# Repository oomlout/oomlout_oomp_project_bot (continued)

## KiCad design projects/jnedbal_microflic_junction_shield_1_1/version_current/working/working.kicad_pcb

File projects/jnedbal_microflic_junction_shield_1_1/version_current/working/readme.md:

# MicroFLiC_junction_shield_1_1 by jnedbal  
This is a harvested standardized copy of a project from github.  
The original project can be found at:  
https://github.com/jnedbal/MicroFLiC_junction_shield_1_1  
Please consult that link for additional, details, files, and license information.  
Note: It was auto harvested and if the original repo had more than one board file or anything out of the ordinary the files here are likely not representative.

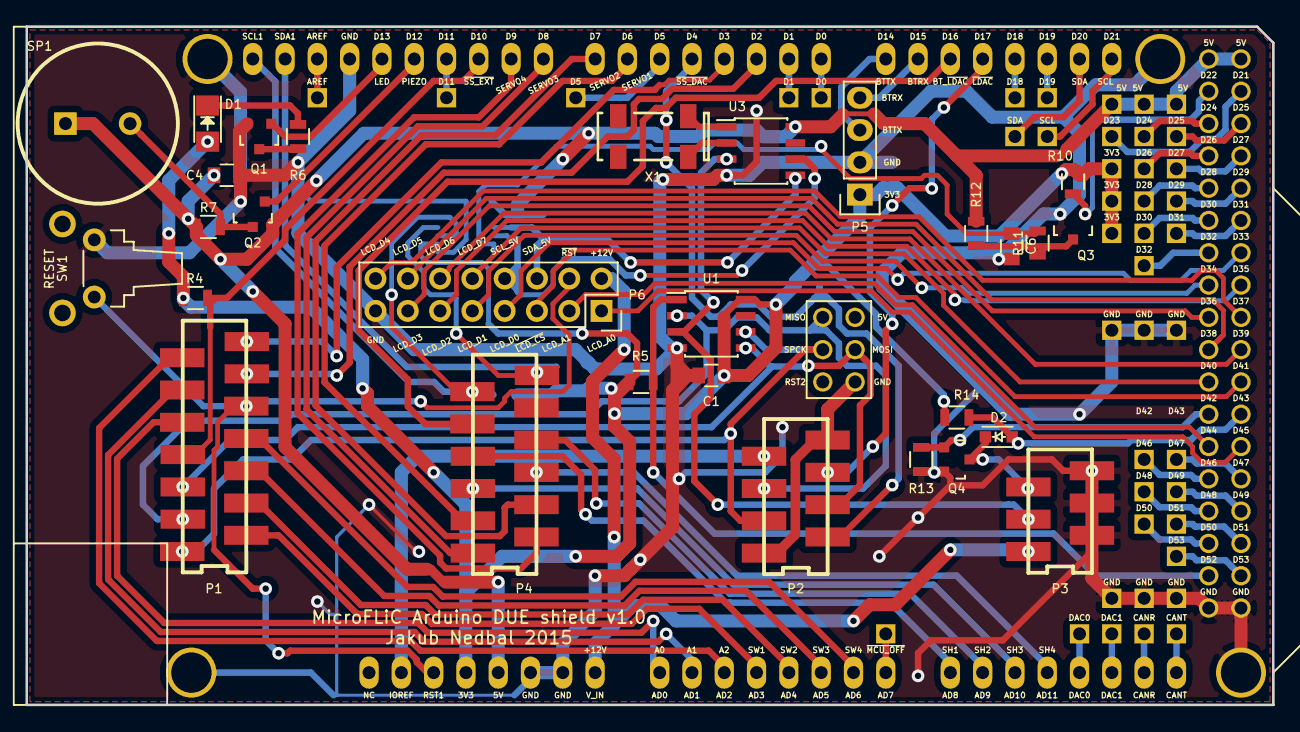
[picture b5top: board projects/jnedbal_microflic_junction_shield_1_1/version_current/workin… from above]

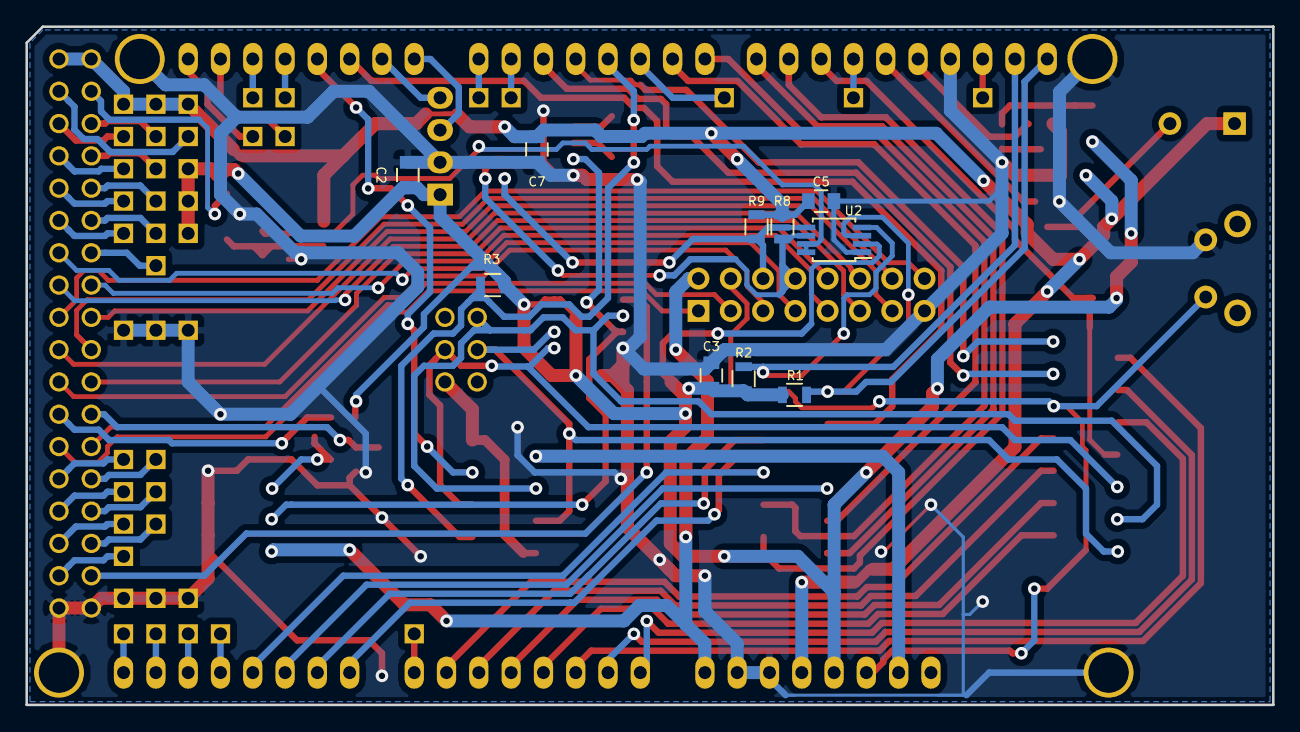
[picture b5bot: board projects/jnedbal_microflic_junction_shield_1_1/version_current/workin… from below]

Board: 2 copper layers, 98.0 x 53.3 mm, 83 parts (10 on the bottom side), 94 nets.

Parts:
A1: Arduino DUE; ARDUINO_DUE
C1, C2, C3, C4, C5, C7: 100n; C_0805
C6: 100p; C_0805
D1: LED; LED-1206
D2: 1N4148; SOD-323
P1: 14-way Micro-MaTch; 1-188275-4
P2: 8-way Micro-MaTch; 7-188275-8
P3: 6-way Micro-MaTch; 7-188275-6
P4: 12-way Micro-MaTch; 1-188275-2
P5: 1x4 socket strip R/A; Socket_Strip_Straight_1x04
P6: 2x8 socket strip; Socket_Strip_Straight_2x08
PP1, PP2, PP3, PP4, PP5, PP6, PP7, PP8, PP9, PP10, PP11, PP12, PP13, PP14, PP15, PP16, PP17, PP18, PP19, PP20, PP21, PP22, PP23, PP24, PP25, PP26, PP27, PP28, PP29, PP30, PP31, PP32, PP33, PP34, PP35, PP36, PP37, PP38, PP39, PP40, PP41, PP42, PP43: CONN_01X01; PIN_ARRAY_1
Q1, Q2, Q3, Q4: TSM2314; SOT-23
R1, R2, R6, R7, R8, R9: 1k5; R_0805
R3, R4, R5, R10, R11, R12, R13, R14: 100k; R_0805
SP1: Piezo sounder; piezo
SW1: Tactile switch R/A; tactileSwitchRA
U1: 23LCV1024; SOIC-8_3.9x4.9mm_Pitch1.27mm
U2: PCA9306; MSOP-8_3x3mm_Pitch0.65mm
U3: DS1338; SOIC-8_3.9x4.9mm_Pitch1.27mm
X1: 32.768kHz; Crystal_8.7*3.7mm

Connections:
+3V3: A1.3V3, C1.1, C2.1, C3.1, D1.2, P5.1, PP32.1, PP33.1, PP34.1, R1.1, R2.1, R3.1, R4.1, R5.1, R10.2, R14.1, U1.8, U2.2
+5V: A1.5V, A1.5V_4, A1.5V_5, C4.1, C5.1, C7.1, PP35.1, PP36.1, PP37.1, R7.1, R8.2, R9.2, R12.2, SP1.1, U3.8
+12V: A1.V_IN, P3.1, P6.2
+BATT: P3.3, U1.3, U3.3
/A0: A1.AD0, P1.9
/A1: A1.AD1, P1.11
/A2: A1.AD2, P1.13
/AD7: A1.AD7, PP1.1
/AREF: A1.AREF, PP13.1
/BTRX: A1.15, P5.4
/BTTX: A1.14, P5.3
/CANR: A1.CANR, PP4.1
/CANT: A1.CANT, PP5.1
/D0: A1.0, PP17.1
/D1: A1.1, PP16.1
/D2: A1.2, P1.12
/D3: A1.3, P1.14
/D5: A1.5, PP15.1
/D11: A1.11, PP14.1
/D18: A1.18, PP18.1
/D19: A1.19, PP19.1
/D23: A1.23, PP22.1
/D24: A1.24, PP23.1
/D25: A1.25, PP24.1
/D26: A1.26, PP25.1
/D27: A1.27, PP26.1
/D28: A1.28, PP27.1
/D29: A1.29, PP28.1
/D30: A1.30, PP29.1
/D31: A1.31, PP30.1
/D32: A1.32, PP31.1
/D46: A1.46, PP12.1
/D47: A1.47, PP11.1
/D48: A1.48, PP10.1
/D49: A1.49, PP9.1
/D50: A1.50, PP8.1
/D51: A1.51, PP7.1
/D53: A1.53, PP6.1
/DAC0: A1.DAC0, PP2.1
/DAC1: A1.DAC1, PP3.1
/IOREF: A1.IOR, P2.7
/LCDandRTC/I2C_EN: C6.1, R11.2, U2.7, U2.8
/LCDandRTC/LCD_A0: A1.45, P6.1
/LCDandRTC/LCD_A1: A1.44, P6.3
/LCDandRTC/LCD_D0: A1.33, P6.7
/LCDandRTC/LCD_D1: A1.34, P6.9
/LCDandRTC/LCD_D2: A1.35, P6.11
/LCDandRTC/LCD_D3: A1.36, P6.13
/LCDandRTC/LCD_D4: A1.37, P6.16
/LCDandRTC/LCD_D5: A1.38, P6.14
/LCDandRTC/LCD_D6: A1.39, P6.12
/LCDandRTC/LCD_D7: A1.40, P6.10
/LCDandRTC/SCL1: A1.SCL1, P4.11, R1.2, U2.3
/LCDandRTC/SCL_5V: P6.8, R8.1, U2.6, U3.6
/LCDandRTC/SDA1: A1.SDA1, P4.12, R2.2, U2.4
/LCDandRTC/SDA_5V: P6.6, R9.1, U2.5, U3.5
/LCDandRTC/X1: U3.1, X1.1
/LCDandRTC/X2: U3.2, X1.4
/LCDandRTC/~I2C_EN: A1.22, Q3.1, R10.1
/LCDandRTC/~LCD_CS: A1.41, P6.5
/LCDandRTC/~RST: A1.RST1, P1.10, P6.4, SW1.2
/MCUswitch/PWR_OFF: A1.42, Q4.1, R13.1
/MCUswitch/~MCU_OFF: D2.1, P3.5, Q4.3
/MCUswitch/~SW_SENSE: A1.43, D2.2, R14.2
/MISO: A1.MISO, P1.3, P2.5, U1.2
/MOSI: A1.MOSI, P1.5, P2.4, U1.5
/SCL: A1.21, PP21.1
/SDA: A1.20, PP20.1
/SERVO1: A1.6, P4.3
/SERVO2: A1.7, P4.4
/SERVO3: A1.8, P4.1
/SERVO4: A1.9, P4.2
/SH1: A1.AD8, P4.7
/SH2: A1.AD9, P4.8
/SH3: A1.AD10, P4.5
/SH4: A1.AD11, P4.6
/SH_~LDAC: A1.16, P4.9
/SPCK: A1.SPCK, P1.1, P2.3, U1.6
/SW1: A1.AD3, P1.2
/SW2: A1.AD4, P1.4
/SW3: A1.AD5, P1.6
/SW4: A1.AD6, P1.8
/humanInterface/LED13: A1.13, Q1.1
/humanInterface/PIEZO12: A1.12, Q2.1
/~LDAC: A1.17, P2.6
/~SS_DAC: A1.4, P2.2, R3.2
/~SS_EXT: A1.10, P1.7, R4.2
/~SS_NVRAM: A1.52, R5.2, U1.1
GND: A1.GND1, A1.GND2, A1.GND3, A1.GND4, A1.GND5, C1.2, C2.2, C3.2, C4.2, C5.2, C6.2, C7.2, P3.2, P3.4, P3.6, P5.2, P6.15, PP38.1, PP39.1, PP40.1, PP41.1, PP42.1, PP43.1, Q1.2, Q2.2, Q3.2, Q4.2, R13.2, SW1.1, U1.4, U2.1, U3.4
GNDREF: A1.GND6, P2.1, P2.8
unnamed: D1.1, R6.1
unnamed: Q1.3, R6.2
unnamed: Q2.3, R7.2, SP1.2
unnamed: Q3.3, R11.1, R12.1

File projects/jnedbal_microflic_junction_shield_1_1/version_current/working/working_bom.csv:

"Id";"Designator";"Footprint";"Quantity";"Designation";"Supplier and ref";
1;"C1,C2,C3,C4,C5,C7";"C_0805";6;"100n";;;
2;"C6";"C_0805";1;"100p";;;
3;"D1";"LED-1206";1;"LED";;;
4;"P1";"1-188275-4";1;"14-way Micro-MaTch";;;
5;"P2";"7-188275-8";1;"8-way Micro-MaTch";;;
6;"P3";"7-188275-6";1;"6-way Micro-MaTch";;;
7;"P4";"1-188275-2";1;"12-way Micro-MaTch";;;
8;"P5";"Socket_Strip_Straight_1x04";1;"1x4 socket strip R/A";;;
9;"P6";"Socket_Strip_Straight_2x08";1;"2x8 socket strip";;;
10;"PP2,PP3,PP4,PP5,PP6,PP7,PP8,PP9,PP10,PP11,PP12,PP13,PP14,PP15,PP16,PP17,PP18,PP19,PP22,PP23,PP24,PP25,PP26,PP27,PP28,PP29,PP30,PP31,PP32,PP34,PP33,PP35,PP36,PP37,PP39,PP40,PP38,PP41,PP42,PP43,PP1,PP21,PP20";"PIN_ARRAY_1";43;"CONN_01X01";;;
11;"Q1,Q2,Q3,Q4";"SOT-23";4;"TSM2314";;;
12;"R1,R2,R6,R7,R8,R9";"R_0805";6;"1k5";;;
13;"R3,R4,R5,R10,R11,R12,R13,R14";"R_0805";8;"100k";;;
14;"U1";"SOIC-8_3.9x4.9mm_Pitch1.27mm";1;"23LCV1024";;;
15;"U2";"MSOP-8_3x3mm_Pitch0.65mm";1;"PCA9306";;;
16;"U3";"SOIC-8_3.9x4.9mm_Pitch1.27mm";1;"DS1338";;;
17;"X1";"Crystal_8.7*3.7mm";1;"32.768kHz";;;
18;"SP1";"piezo";1;"Piezo sounder";;;
19;"SW1";"tactileSwitchRA";1;"Tactile switch R/A";;;
20;"A1";"ARDUINO_DUE";1;"Arduino DUE";;;
21;"D2";"SOD-323";1;"1N4148";;;

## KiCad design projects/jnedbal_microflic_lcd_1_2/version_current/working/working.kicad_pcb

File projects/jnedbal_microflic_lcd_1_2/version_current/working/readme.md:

# MicroFLiC_LCD_1_2 by jnedbal  
This is a harvested standardized copy of a project from github.  
The original project can be found at:  
https://github.com/jnedbal/MicroFLiC_LCD_1_2  
Please consult that link for additional, details, files, and license information.  
Note: It was auto harvested and if the original repo had more than one board file or anything out of the ordinary the files here are likely not representative.

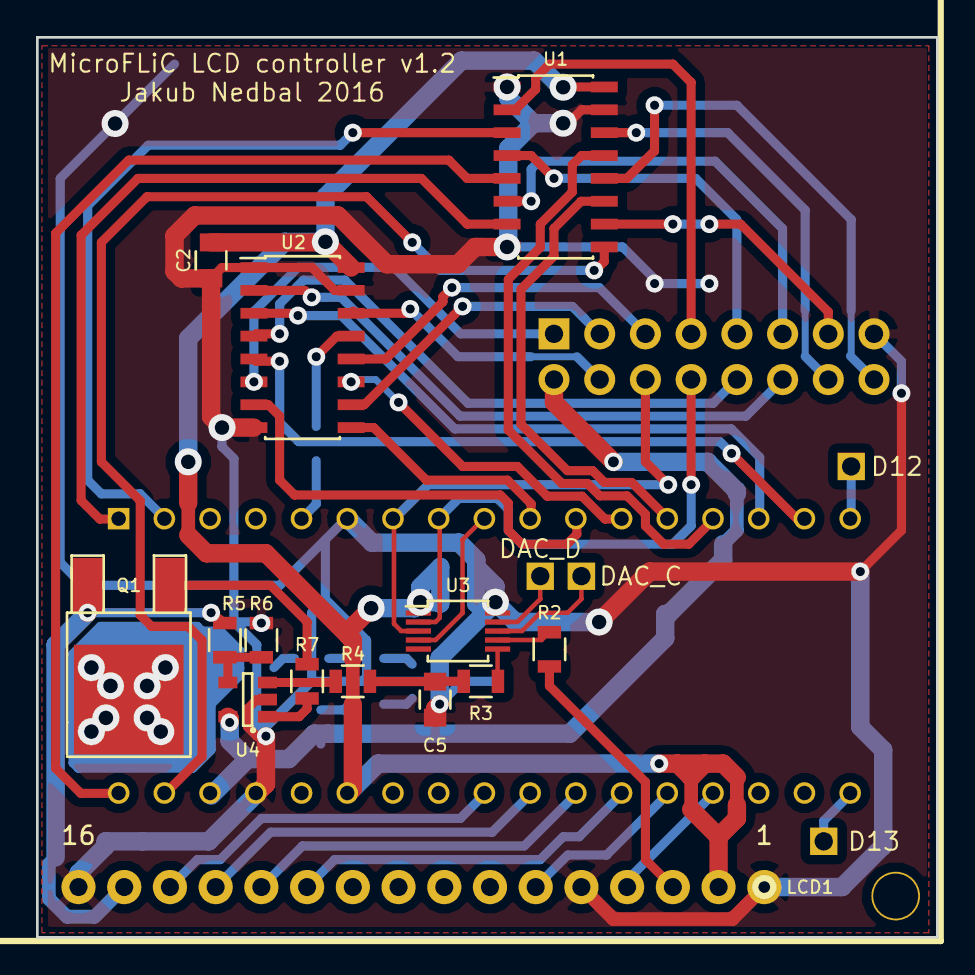
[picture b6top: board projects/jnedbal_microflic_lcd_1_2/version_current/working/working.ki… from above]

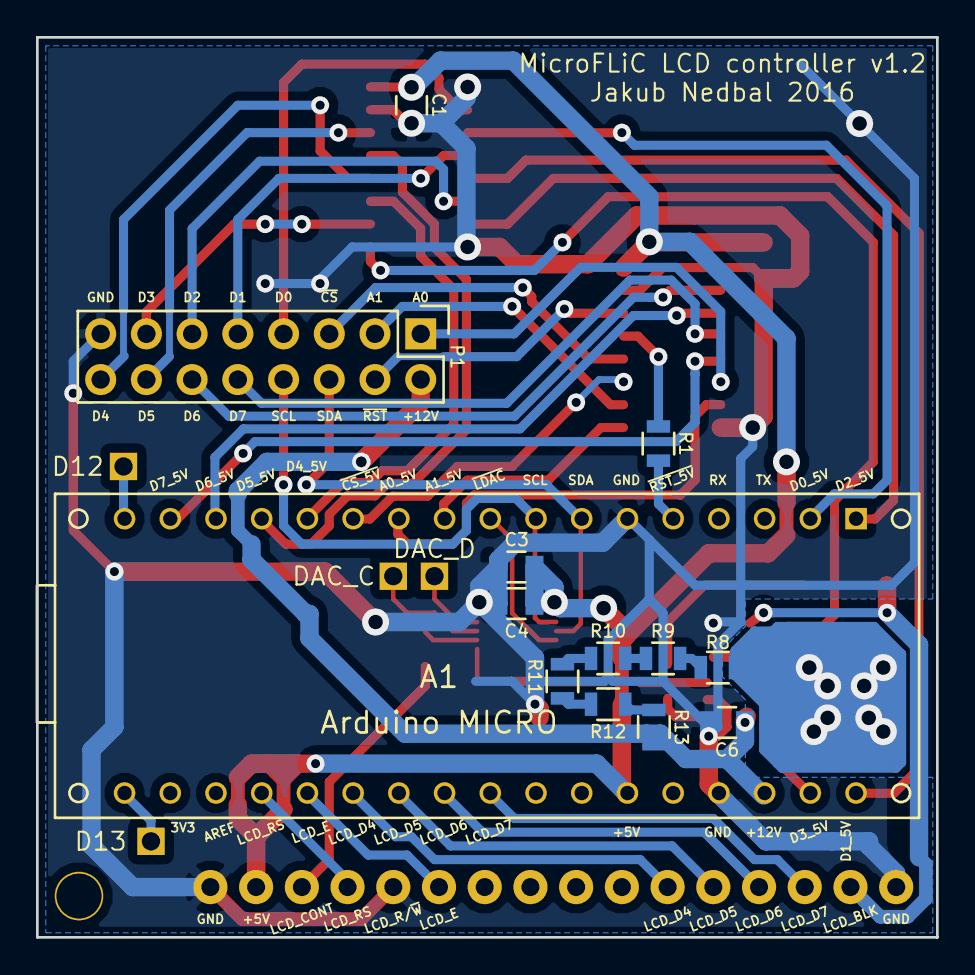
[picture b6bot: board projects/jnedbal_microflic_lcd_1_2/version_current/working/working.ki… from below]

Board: 2 copper layers, 50.0 x 50.0 mm, 31 parts (13 on the bottom side), 56 nets.

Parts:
A1: Arduino MICRO; ArduinoMicro
C1, C2, C4, C6: 100n; C_0805
C3, C5: 4u7/25V; C_0805
LCD1: LCD2004
P1: 2x8 header strip; Pin_Header_Straight_2x08
PP1, PP2, PP3, PP4: CONN_01X01; PIN_ARRAY_1
Q1: MJD31CT4G; TO-252-2Lead
R1: 1k5; R_0805
R2, R7: 47R; R_0805
R3: 100k; R_0805
R4, R5, R6: 10k; R_0805
R8, R9, R10, R11, R12, R13: 6R8; R_0805
U1, U2: 74AHCT367; SOIC-16_3.9x9.9mm_Pitch1.27mm
U3: MCP4728; MSOP-10_3x3mm_Pitch0.5mm
U4: TLV2371; SOT-23-5

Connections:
+5V: A1.5V, C1.1, C2.1, C3.1, C4.1, LCD1.2, U1.16, U2.16, U3.1
+12V: A1.VI, C6.1, P1.2, R13.1, U4.5
/3V3to5V/A0: P1.1, U2.6
/3V3to5V/A0_5V: A1.6, U2.7
/3V3to5V/A1: P1.3, U2.10
/3V3to5V/A1_5V: A1.5, U2.9
/3V3to5V/D0: P1.7, U1.2
/3V3to5V/D0_5V: A1.SS, U1.3
/3V3to5V/D1: P1.9, U1.4
/3V3to5V/D1_5V: A1.SCK, U1.5
/3V3to5V/D2: P1.11, U1.6
/3V3to5V/D2_5V: A1.MO, U1.7
/3V3to5V/D3: P1.13, U1.10
/3V3to5V/D3_5V: A1.MI, U1.9
/3V3to5V/D4: P1.16, U1.12
/3V3to5V/D4_5V: A1.8, U1.11
/3V3to5V/D5: P1.14, U1.14
/3V3to5V/D5_5V: A1.9, U1.13
/3V3to5V/D6: P1.12, U2.2
/3V3to5V/D6_5V: A1.10, U2.3
/3V3to5V/D7: P1.10, U2.4
/3V3to5V/D7_5V: A1.11, U2.5
/3V3to5V/~CS: P1.5, U2.12
/3V3to5V/~CS_5V: A1.7, U2.11
/3V3to5V/~RST: P1.4, U2.14
/3V3to5V/~RST_5V: A1.RST1, R1.1
/D12: A1.12, PP1.1
/D13: A1.13, PP2.1
/DAC/DAC_C: PP3.1, U3.8
/DAC/DAC_D: PP4.1, U3.9
/DAC/LCD_BKL: LCD1.15, Q1.3, R6.1
/DAC/LCD_BKL_CTRL: R3.2, U3.6
/DAC/LCD_CONT: LCD1.3, R2.1
/DAC/SCL: A1.3, P1.8, U3.2
/DAC/SDA: A1.2, P1.6, U3.3
/DAC/~LDAC: A1.4, U3.4
/LCD_D4: A1.A2, LCD1.11
/LCD_D5: A1.A3, LCD1.12
/LCD_D6: A1.A4, LCD1.13
/LCD_D7: A1.A5, LCD1.14
/LCD_E: A1.A1, LCD1.6
/LCD_RS: A1.A0, LCD1.4
GND: A1.GND, C1.2, C2.2, C3.2, C4.2, C5.2, C6.2, LCD1.1, LCD1.5, LCD1.16, P1.15, R5.2, U1.1, U1.8, U1.15, U2.1, U2.8, U2.15, U3.10, U4.2
unnamed: C5.1, R3.1, R4.2
unnamed: Q1.1, R7.1
unnamed: Q1.2, R8.2
unnamed: R1.2, U2.13
unnamed: R2.2, U3.7
unnamed: R4.1, U4.3
unnamed: R5.1, R6.2, U4.4
unnamed: R7.2, U4.1
unnamed: R8.1, R9.2
unnamed: R10.1, R11.2
unnamed: R9.1, R10.2
unnamed: R11.1, R12.2
unnamed: R12.1, R13.2

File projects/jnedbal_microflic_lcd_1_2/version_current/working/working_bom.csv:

"Id";"Designator";"Footprint";"Quantity";"Designation";"Supplier and ref";
1;"C3,C5";"C_0805";2;"4u7/25V";;;
2;"C4,C6,C1,C2";"C_0805";4;"100n";;;
3;"PP1,PP2,PP3,PP4";"PIN_ARRAY_1";4;"CONN_01X01";;;
4;"R2,R7";"R_0805";2;"47R";;;
5;"U3";"MSOP-10_3x3mm_Pitch0.5mm";1;"MCP4728";;;
6;"U4";"SOT-23-5";1;"TLV2371";;;
7;"P1";"Pin_Header_Straight_2x08";1;"2x8 header strip";;;
8;"U1,U2";"SOIC-16_3.9x9.9mm_Pitch1.27mm";2;"74AHCT367";;;
9;"Q1";"TO-252-2Lead";1;"MJD31CT4G";;;
10;"R3";"R_0805";1;"100k";;;
11;"R4,R5,R6";"R_0805";3;"10k";;;
12;"R1";"R_0805";1;"1k5";;;
13;"A1";"ArduinoMicro";1;"Arduino MICRO";;;
14;"LCD1";"LCD2004";1;"LCD2004";;;
15;"R8,R9,R10,R11,R12,R13";"R_0805";6;"6R8";;;

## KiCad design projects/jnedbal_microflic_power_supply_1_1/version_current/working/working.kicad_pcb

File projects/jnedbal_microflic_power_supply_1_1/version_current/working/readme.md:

# OOMP Project  
## MicroFLiC_power_supply_1_1  by jnedbal  
  
oomp key: oomp_projects_flat_jnedbal_microflic_power_supply_1_1  
(snippet of original readme)  

  full source readme at [readme_src.md](readme_src.md)  
  
source repo at: [https://github.com/jnedbal/MicroFLiC_power_supply_1_1](https://github.com/jnedbal/MicroFLiC_power_supply_1_1)  
## Board  

## Schematic  

[schematic pdf](working_schematic.pdf)  
## Images

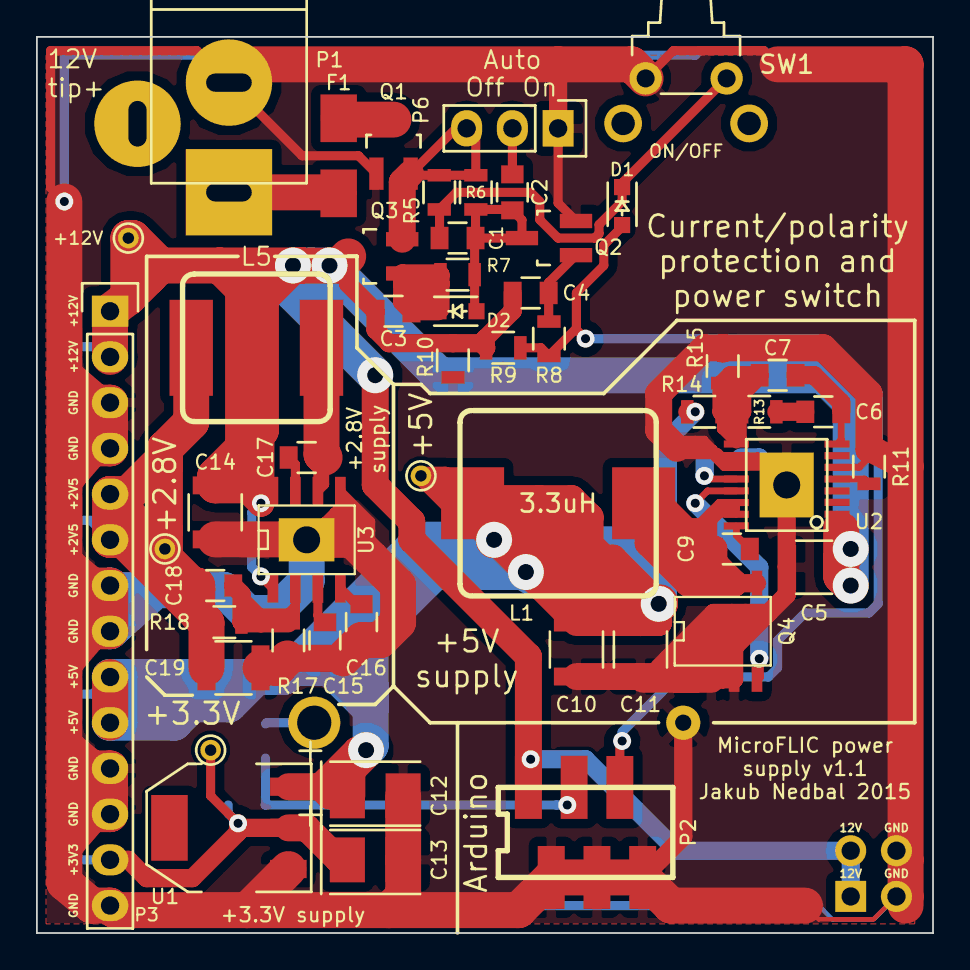
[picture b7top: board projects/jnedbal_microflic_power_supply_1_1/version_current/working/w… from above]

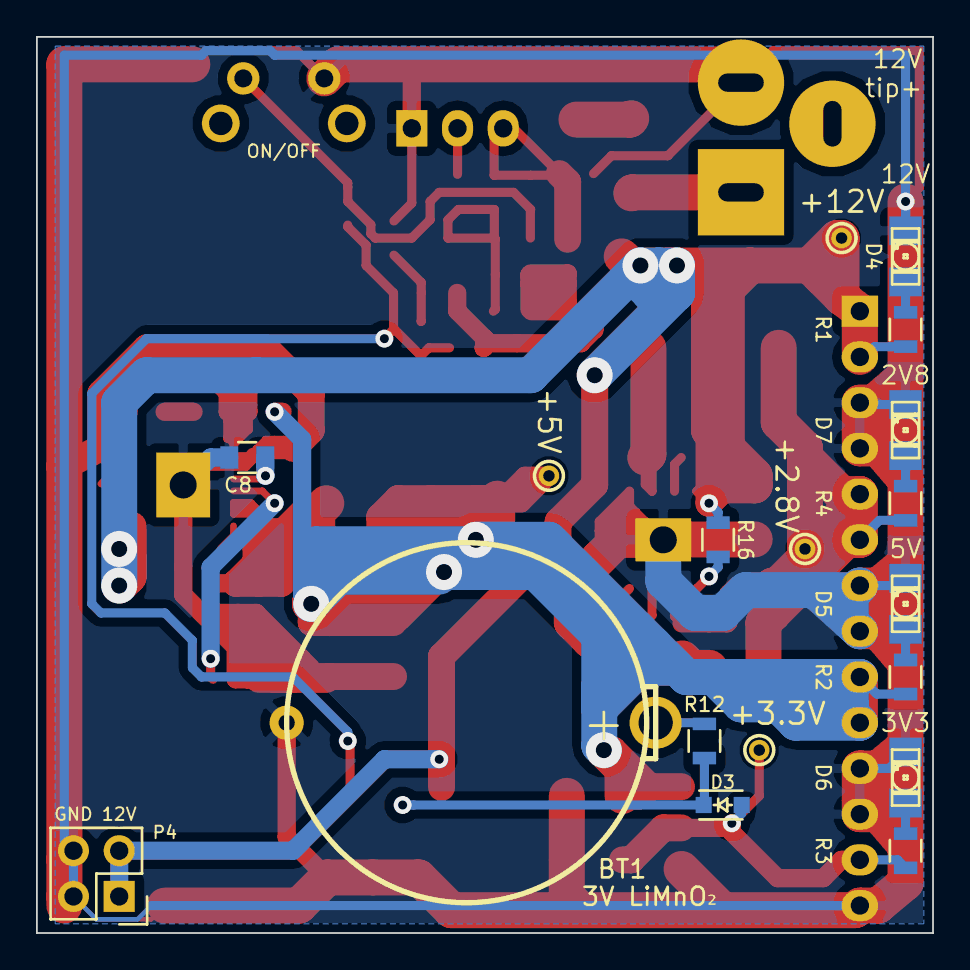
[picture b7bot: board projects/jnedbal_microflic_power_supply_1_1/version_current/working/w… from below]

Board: 2 copper layers, 49.8 x 49.8 mm, 65 parts (14 on the bottom side), 34 nets.

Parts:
BT1: 3V LiMnO₂; ML2016
C1, C8, C15: 1u/50V; C_0805
C2, C9, C17: 100n; C_0805
C3: 10n; C_0805
C4: 4u7/25V; C_0805
C5, C14: 22u/25V; C_1210
C6: 680p; C_0805
C7: 1p5; C_0805
C10, C11, C19: 47u/16V; C_1210
C12, C13: 10u/10V/0.15Ω<ESR<0.5Ω; TantalC_SizeB_EIA-3528_Reflow
C16: 8n2; C_0805
C18: 4p7; C_0805
D1, D2, D3: 1N4148; SOD-323
D4, D5, D6, D7: LED; LED-1206
F1: F5A; Fuse_SMD1206_HandSoldering
L1: 3.3uH; IHLP-4040DZ-01
L5: 2.2uH; IHLP-3232CZ-11
P1: DC jack; JACK_ALIM
P2: 6-way Micro-MaTch; 7-188275-6
P3: 1x14 socket strip; ESQ-114-33-S-G
P4: 2x2 socket strip; ESQ-102-33-D-G
P6: 1x3 header strip; Pin_Header_Straight_1x03
PP1: +12V; PINTST
PP2: +5V; PINTST
PP3: +3.3V; PINTST
PP4: +2.8V; PINTST
Q1, Q3: SI2369; SOT23GDS
Q2: TSM2314; SOT23GDS
Q4: IRF8721; SO8_FDS6298
R1, R10, R16: 10k; R_0805
R2, R15: 3k; R_0805
R3: 1k5; R_0805
R4: 1k; R_0805
R5, R6, R7, R9: 100k; R_0805
R8: 270k; R_0805
R11, R13: 82k; R_0805
R12: 470R; R_0805
R14: 22k; R_0805
R17: 12k; R_0805
R18: 33k; R_0805
SW1: Tactile switch R/A; tactileSwitchRA
U1: AP1117E33; SOT-223
U2: ADP2381; SSOP-16(EP)
U3: TPS54428; PDSO8

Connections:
+2V5: C18.1, C19.1, L5.2, P3.5, P3.6, PP4.1, R4.1, R18.1
+3V3: C13.1, D3.2, P3.13, PP3.1, R3.1, U1.2
+5VP: C10.1, C11.1, C12.1, L1.2, P3.9, P3.10, PP2.1, R2.1, R14.1, U1.3
+12V: C3.1, C4.1, C5.1, C14.1, P2.1, P3.1, P3.2, P4.1, P4.2, PP1.1, Q3.D, R1.1, R9.1, R10.1, R16.1, U2.1, U2.2, U3.8
+BATT: D3.1, P2.3, R12.1
/Power Supply/BST: C9.1, U2.16
/Power Supply/C7R8: C6.2, R13.1
/Power Supply/COMP: C6.1, C7.1, U2.8
/Power Supply/EN: R16.2, U3.1
/Power Supply/FB: C7.2, R13.2, R14.2, R15.1, U2.9
/Power Supply/LD: Q4.G, U2.13
/Power Supply/RT: R11.2, U2.5
/Power Supply/SS: C16.1, U3.4
/Power Supply/SW2.8: C17.1, L5.1, U3.6
/Power Supply/SW5: C9.2, L1.1, Q4.D, U2.14, U2.15
/Power Supply/VBST: C17.2, U3.7
/Power Supply/VFB: C18.2, R17.1, R18.2, U3.2
/Power Supply/VREG2.8: C15.1, U3.3
/Power Supply/VREG5: C8.1, U2.12
/electronicSwitch/AUTO: C2.2, P6.2
/electronicSwitch/CURLIM: C3.2, D2.1, Q3.G, R7.2
/electronicSwitch/DELAYED_OFF: C4.2, Q2.G, R8.1
/electronicSwitch/MCU_OFF: D1.2, P2.5, R8.2, R9.2
/electronicSwitch/PUSHBUTTON: C1.2, D1.1, R5.2, SW1.2
/electronicSwitch/V_5AMP: F1.2, Q1.D
/electronicSwitch/V_IN: F1.1, P1.1
/electronicSwitch/V_PROTECTED: P6.3, Q1.S, Q3.S, R5.1, R6.1
GND: BT1.2, C5.2, C8.2, C10.2, C11.2, C12.2, C13.2, C14.2, C15.2, C16.2, C19.2, D4.1, D5.1, D6.1, D7.1, P1.2, P2.2, P2.4, P2.6, P3.3, P3.4, P3.7, P3.8, P3.11, P3.12, P3.14, P4.3, P4.4, P6.1, Q1.G, Q2.S, Q4.S, R10.2, R11.1, R15.2, R17.2, SW1.1, U1.1, U2.6, U2.10, U2.11, U2.17, U3.5, U3.9
unnamed: BT1.1, R12.2
unnamed: C1.1, C2.1, D2.2, Q2.D, R6.2, R7.1
unnamed: D4.2, R1.2
unnamed: D5.2, R2.2
unnamed: D6.2, R3.2
unnamed: D7.2, R4.2

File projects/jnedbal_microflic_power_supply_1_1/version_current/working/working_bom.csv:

"Id";"Designator";"Footprint";"Quantity";"Designation";"Supplier and ref";
1;"F1";"Fuse_SMD1206_HandSoldering";1;"F5A";;;
2;"D4,D6,D5,D7";"LED-1206";4;"LED";;;
3;"BT1";"ML2016";1;"3V LiMnO₂";;;
4;"L1";"IHLP-4040DZ-01";1;"3.3uH";;;
5;"L5";"IHLP-3232CZ-11";1;"2.2uH";;;
6;"P1";"JACK_ALIM";1;"DC jack";;;
7;"P2";"7-188275-6";1;"6-way Micro-MaTch";;;
8;"P6";"Pin_Header_Straight_1x03";1;"1x3 header strip";;;
9;"SW1";"tactileSwitchRA";1;"Tactile switch R/A";;;
10;"U1";"SOT-223";1;"AP1117E33";;;
11;"C16";"C_0805";1;"8n2";;;
12;"C15,C1,C8";"C_0805";3;"1u/50V";;;
13;"R17";"R_0805";1;"12k";;;
14;"C19,C10,C11";"C_1210";3;"47u/16V";;;
15;"R18";"R_0805";1;"33k";;;
16;"C14,C5";"C_1210";2;"22u/25V";;;
17;"C18";"C_0805";1;"4p7";;;
18;"C2,C9,C17";"C_0805";3;"100n";;;
19;"C3";"C_0805";1;"10n";;;
20;"C4";"C_0805";1;"4u7/25V";;;
21;"C12,C13";"TantalC_SizeB_EIA-3528_Reflow";2;"10u/10V/0.15Ω<ESR<0.5Ω";;;
22;"C6";"C_0805";1;"680p";;;
23;"C7";"C_0805";1;"1p5";;;
24;"R5,R6,R7,R9";"R_0805";4;"100k";;;
25;"R8";"R_0805";1;"270k";;;
26;"R11,R13";"R_0805";2;"82k";;;
27;"R12";"R_0805";1;"470R";;;
28;"R14";"R_0805";1;"22k";;;
29;"R15,R2";"R_0805";2;"3k";;;
30;"R16,R1,R10";"R_0805";3;"10k";;;
31;"U3";"PDSO8";1;"TPS54428";;;
32;"R3";"R_0805";1;"1k5";;;
33;"R4";"R_0805";1;"1k";;;
34;"PP1";"PINTST";1;"+12V";;;
35;"PP2";"PINTST";1;"+5V";;;
36;"PP3";"PINTST";1;"+3.3V";;;
37;"PP4";"PINTST";1;"+2.8V";;;
38;"U2";"SSOP-16(EP)";1;"ADP2381";;;
39;"Q4";"SO8_FDS6298";1;"IRF8721";;;
40;"Q1,Q3";"SOT23GDS";2;"SI2369";;;
41;"Q2";"SOT23GDS";1;"TSM2314";;;
42;"P3";"ESQ-114-33-S-G";1;"1x14 socket strip";;;
43;"P4";"ESQ-102-33-D-G";1;"2x2 socket strip";;;
44;"D1,D2,D3";"SOD-323";3;"1N4148";;;

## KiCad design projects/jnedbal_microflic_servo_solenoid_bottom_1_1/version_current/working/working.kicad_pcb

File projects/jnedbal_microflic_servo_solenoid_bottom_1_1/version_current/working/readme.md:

# OOMP Project  
## MicroFLiC_servo_solenoid_bottom_1_1  by jnedbal  
  
oomp key: oomp_projects_flat_jnedbal_microflic_servo_solenoid_bottom_1_1  
(snippet of original readme)  

  full source readme at [readme_src.md](readme_src.md)  
  
source repo at: [https://github.com/jnedbal/MicroFLiC_servo_solenoid_bottom_1_1](https://github.com/jnedbal/MicroFLiC_servo_solenoid_bottom_1_1)  
## Board  

## Schematic  

[schematic pdf](working_schematic.pdf)  
## Images

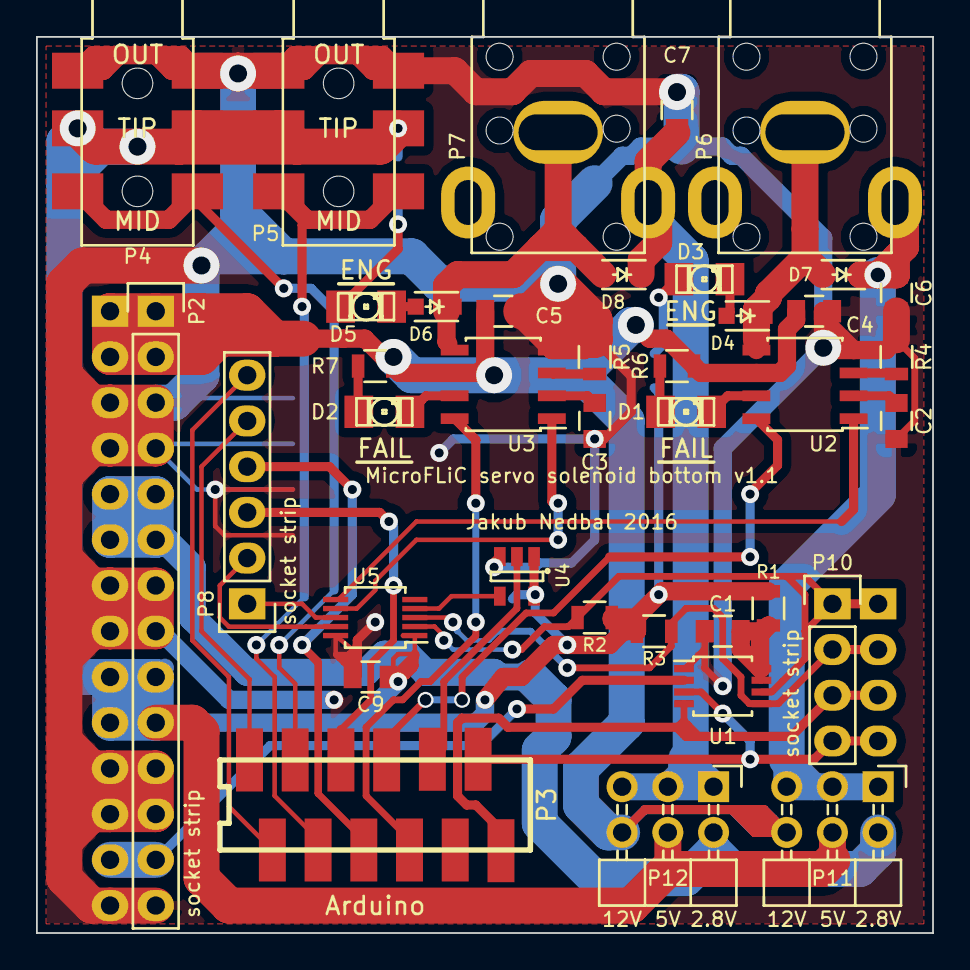
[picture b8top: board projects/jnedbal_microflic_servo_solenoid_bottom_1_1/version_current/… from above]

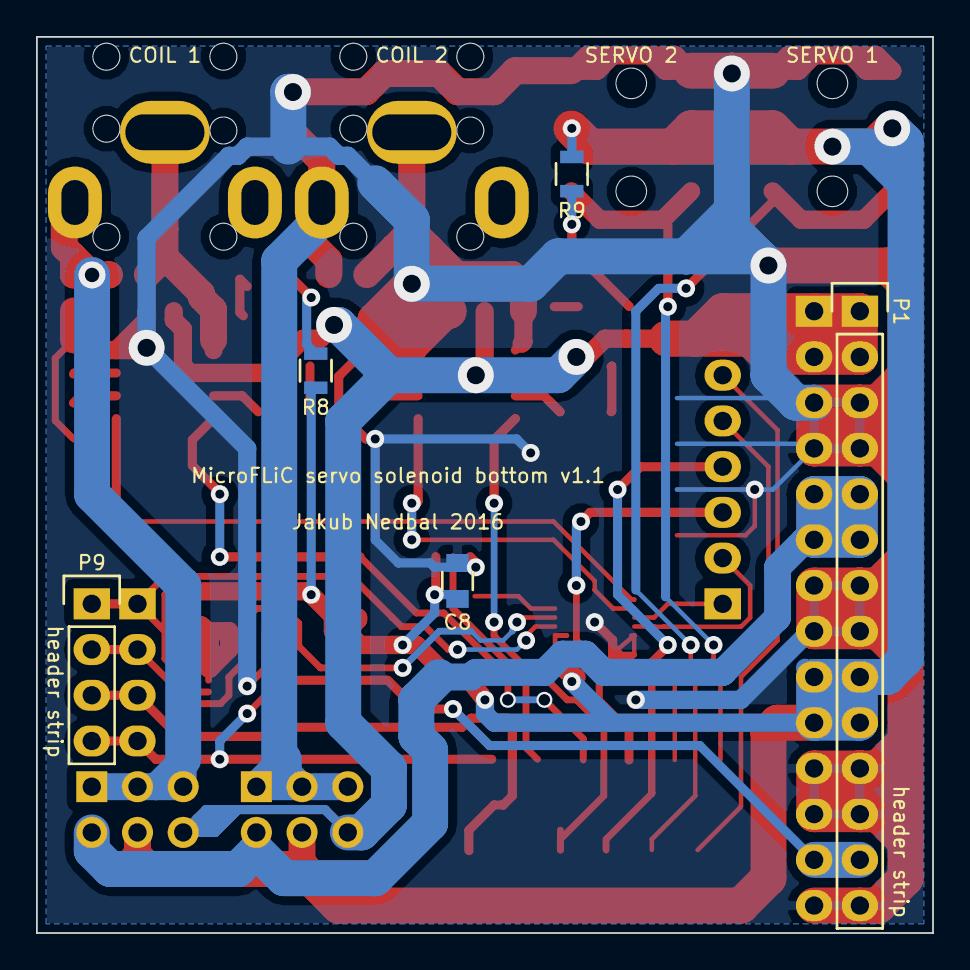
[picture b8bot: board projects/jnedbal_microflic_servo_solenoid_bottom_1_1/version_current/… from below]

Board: 2 copper layers, 49.8 x 49.8 mm, 43 parts (5 on the bottom side), 40 nets.

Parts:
C1: 100p; C_0805
C2, C3: 10n; C_0805
C4, C5, C6, C7: 4u7/25V; C_0805
C8, C9: 100n; C_0805
D1, D2: LED RED; LED-1206
D3, D5: LED YELLOW; LED-1206
D4, D6, D7, D8: 1N4148; SOD-323
P1: 1x14 header strip; Pin_Header_Straight_1x14
P2: 1x14 socket strip; ESQ-114-33-G-S
P3: 12-way Micro-MaTch; 1-188275-2
P4, P5: 3.5mm jack; MJ4435-R
P6, P7: RCA jack; PSG01544
P8: 1x6 socket strip; ESQ-106-33-G-S
P9: 1x4 header strip; Pin_Header_Straight_1x04
P10: 1x4 socket strip; ESQ-104-33-G-S
P11, P12: 2x3 header strip R/A; Pin_Header_Angled_2x03
R1, R4, R5: 270k; R_0805
R2, R3: 1k5; R_0805
R6, R7: 10k; R_0805
R8, R9: 3k; R_0805
U1: PCA9306DP; TSSOP-8_3x3mm_Pitch0.65mm
U2, U3: DRV103; SOIC-8_3.9x4.9mm_Pitch1.27mm
U4: 74HCT1G125; SOT-23-5
U5: MCP4728; MSOP-10_3x3mm_Pitch0.5mm

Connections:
+2V5: P1.5, P1.6, P2.5, P2.6, P11.2, P12.2
+3V3: P1.13, P2.13, U1.2
+5VP: C8.2, C9.2, P1.9, P1.10, P2.9, P2.10, P4.3, P5.3, P11.4, P12.4, R1.1, R2.1, R3.1, R8.2, R9.2, U4.1, U4.5, U5.1
+12V: C4.2, C5.2, P1.1, P1.2, P2.1, P2.2, P11.6, P12.6, R6.2, R7.2, U2.6, U3.6
/I2C/SCL_3V3: P3.11, P9.4, P10.4, U1.3
/I2C/SCL_5V: P9.1, P10.1, R2.2, U1.6, U5.2
/I2C/SDA_3V3: P3.12, P9.3, P10.3, U1.4
/I2C/SDA_5V: P9.2, P10.2, R3.2, U1.5, U5.3
/SERVO1: P3.3, P4.2
/SERVO2: P3.4, P5.2
/SERVO3: P3.1, P8.5
/SERVO4: P3.2, P8.6
/SH3: P3.5, P8.3
/SH4: P3.6, P8.4
/shutterPWM/DA: C2.2, U2.2
/shutterPWM/DB: C3.2, U3.2
/shutterPWM/EA1: D3.2, R8.1
/shutterPWM/EA2: D3.1, D4.2
/shutterPWM/EB1: D5.2, R9.1
/shutterPWM/EB2: D5.1, D6.2
/shutterPWM/FA: D1.2, R6.1
/shutterPWM/FAIL_A: D1.1, U2.7
/shutterPWM/FAIL_B: D2.1, U3.7
/shutterPWM/FB: D2.2, R7.1
/shutterPWM/OA: R4.2, U2.3
/shutterPWM/OB: R5.2, U3.3
/shutterPWM/SH1: P3.7, U2.8
/shutterPWM/SH1_PWM: U2.1, U5.6
/shutterPWM/SH2: P3.8, U3.8
/shutterPWM/SH2_PWM: U3.1, U5.7
/shutterPWM/SH3_PWM: P8.1, U5.8
/shutterPWM/SH4_PWM: P8.2, U5.9
/shutterPWM/SHA_O/C: D4.1, D7.2, P6.1, U2.5
/shutterPWM/SHA_PWR: C6.2, D7.1, P6.2, P11.1, P11.3, P11.5
/shutterPWM/SHB_O/C: D6.1, D8.2, P7.1, U3.5
/shutterPWM/SHB_PWR: C7.2, D8.1, P7.2, P12.1, P12.3, P12.5
/shutterPWM/SH_~LDAC: P3.9, U4.2
GND: C1.2, C2.1, C3.1, C4.1, C5.1, C6.1, C7.1, C8.1, C9.1, P1.3, P1.4, P1.7, P1.8, P1.11, P1.12, P1.14, P2.3, P2.4, P2.7, P2.8, P2.11, P2.12, P2.14, P4.1, P5.1, R4.1, R5.1, U1.1, U2.4, U3.4, U4.3, U5.10
unnamed: C1.1, R1.2, U1.7, U1.8
unnamed: U4.4, U5.4

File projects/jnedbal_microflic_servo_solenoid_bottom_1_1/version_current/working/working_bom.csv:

"Id";"Designator";"Footprint";"Quantity";"Designation";"Supplier and ref";
1;"R9,R8";"R_0805";2;"3k";;;
2;"D3,D5";"LED-1206";2;"LED YELLOW";;;
3;"D2,D1";"LED-1206";2;"LED RED";;;
4;"P12,P11";"Pin_Header_Angled_2x03";2;"2x3 header strip R/A";;;
5;"P6,P7";"PSG01544";2;"RCA jack";;;
6;"P9";"Pin_Header_Straight_1x04";1;"1x4 header strip";;;
7;"U1";"TSSOP-8_3x3mm_Pitch0.65mm";1;"PCA9306DP";;;
8;"U5";"MSOP-10_3x3mm_Pitch0.5mm";1;"MCP4728";;;
9;"P5,P4";"MJ4435-R";2;"3.5mm jack";;;
10;"U2,U3";"SOIC-8_3.9x4.9mm_Pitch1.27mm";2;"DRV103";;;
11;"C1";"C_0805";1;"100p";;;
12;"C2,C3";"C_0805";2;"10n";;;
13;"C4,C5,C6,C7";"C_0805";4;"4u7/25V";;;
14;"C9,C8";"C_0805";2;"100n";;;
15;"R4,R5,R1";"R_0805";3;"270k";;;
16;"R6,R7";"R_0805";2;"10k";;;
17;"P3";"1-188275-2";1;"12-way Micro-MaTch";;;
18;"P1";"Pin_Header_Straight_1x14";1;"1x14 header strip";;;
19;"P2";"ESQ-114-33-G-S";1;"1x14 socket strip";;;
20;"P8";"ESQ-106-33-G-S";1;"1x6 socket strip";;;
21;"P10";"ESQ-104-33-G-S";1;"1x4 socket strip";;;
22;"R2,R3";"R_0805";2;"1k5";;;
23;"U4";"SOT-23-5";1;"74HCT1G125";;;
24;"D4,D6,D7,D8";"SOD-323";4;"1N4148";;;
